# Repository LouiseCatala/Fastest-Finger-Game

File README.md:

# FASTEST FINGER — Made by Catala

This is an **editable KiCad PCB Editor board layout** recreated from the supplied reference image.

**Changes from the reference**
- All six names across the top have been removed.
- The bottom-center text now reads **Made by Catala**.
- The original title, three-player layout, approximate placement, and white decorative graphics are retained.

## PCB 3D Preview

The 3D visualization of the Fastest Finger PCB design created using KiCad.

## Schematic Diagram

The preliminary schematic diagram of the Fastest Finger circuit designed using KiCad Schematic Editor.

## Open in KiCad

1. Extract the whole ZIP; keep the `models` folder with the project files.
2. In KiCad Project Manager choose **File → Open Project** and select `Fastest_Finger_Made_by_Catala.kicad_pro`.
3. Double-click `Fastest_Finger_Made_by_Catala.kicad_pcb` from the project tree, or choose the PCB Editor shortcut.
4. In PCB Editor, use **View → 3D Viewer** (`Alt+3` on many systems) to see the approximate component models.
5. Edit text and locations directly on the **F.SilkS** and other PCB layers.
6. Open **Schematic Editor** to view or modify the `.kicad_sch` file.

Alternatively, start standalone PCB Editor and use **File → Open** to select the `.kicad_pcb` file. Do not try to select `.kicad_pcb` from KiCad Project Manager's **Open Project** file dialog, which filters for `.kicad_pro`.

## Hardware Components

| Component | Quantity |
|-----------|----------|
| Tang Nano 9K FPGA Board | 1 |
| 4-Digit 7-Segment Display | 1 |
| Player Push Buttons | 3 |
| START Button | 1 |
| RESET Button | 1 |
| NPN Transistors | 5 |
| Resistors | 17 |
| Capacitors | 2 |
| Diodes | 4 |
| LEDs | 2 |
| Buzzer | 1 |
| Mounting Holes | 4 |
| Printed Circuit Board | 1 |

## Important Limitation

This is a **visual/layout reconstruction with a preliminary schematic, not a verified, manufacturing-ready electronic design**.

The electrical connections, FPGA pin assignments, component values, and control wiring require verification. PCB traces are not fully routed, and FPGA code is not included.

Do not send the PCB for fabrication or assume functionality without verifying the actual circuit.

Real footprints and dimensions must be checked against the specific parts to be installed, especially the four-digit display, buttons, buzzer, and diodes. Visual models are approximations, not manufacturer STEP models.

- Board nominal dimensions: **174 mm × 128 mm**.
- Tang Nano 9K: represented by a **2 × 24 pin, 2.54 mm pitch** carrier footprint.
- Editable silkscreen labels and PCB features are part of the `.kicad_pcb` file.

---

**Made by Catala**

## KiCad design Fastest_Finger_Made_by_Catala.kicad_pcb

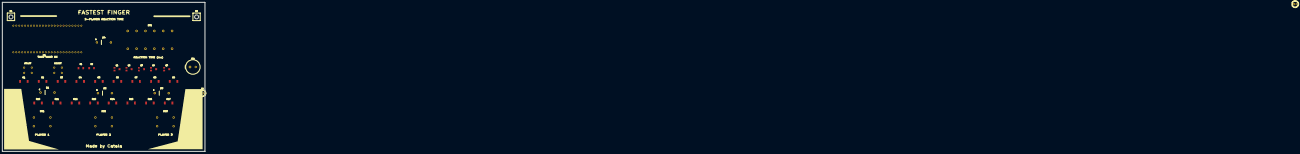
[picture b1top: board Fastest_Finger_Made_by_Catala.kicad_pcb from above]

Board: 2 copper layers, 174.0 x 128.0 mm, 42 parts (0 on the bottom side), 38 nets, no tracks yet.

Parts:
BZ1: Buzzer_TDK_PS1240P02BT_D12.2mm_H6.5mm
C1, C2: Capacitor; Cap_1206
D1, D2, D3, D4: Diode; Diode_DO41_P7.62
D5, D6: LED_D5.0mm
DS1: 4-digit display; Display_4Digit_7Segment_54x21
H1, H2, H3, H4: Mounting Hole; MountingHole_3.4mm
Q1, Q2, Q3, Q4, Q5: Transistor; SOT23_3Pin
R1, R2, R3, R4, R5, R6, R7, R8, R9, R10, R11, R12, R13, R14, R15, R16, R17: R; Resistor_2512
SW1, SW2, SW3: Pushbutton 12 mm; SW_Tact_12mm
SW4, SW5: Pushbutton 6 mm; SW_Tact_6mm
U1: Tang Nano 9K; Tang_Nano_9K_2x24

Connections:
+3V3: BZ1.1, C1.1, C2.1, R13.1, R14.1, R15.1, R16.1, U1.1
BTN_P1: R13.2, SW1.1, U1.3
BTN_P2: R14.2, SW2.1, U1.4
BTN_P3: R15.2, SW3.1, U1.5
BTN_RESET: SW5.1, U1.7
BTN_START: R16.2, SW4.1, U1.6
BUZZ_BASE: Q5.1, R17.2
BUZZ_GPIO: R17.1, U1.20
BUZZ_NEG: BZ1.2, Q5.3
DIG1: DS1.12, Q1.3
DIG1_BASE: Q1.1, R9.2
DIG1_GPIO: R9.1, U1.16
DIG2: DS1.9, Q2.3
DIG2_BASE: Q2.1, R10.2
DIG2_GPIO: R10.1, U1.17
DIG3: DS1.8, Q3.3
DIG3_BASE: Q3.1, R11.2
DIG3_GPIO: R11.1, U1.18
DIG4: DS1.6, Q4.3
DIG4_BASE: Q4.1, R12.2
DIG4_GPIO: R12.1, U1.19
GND: C1.2, C2.2, Q1.2, Q2.2, Q3.2, Q4.2, Q5.2, SW1.2, SW2.2, SW3.2, SW4.2, SW5.2, U1.2
SEG_A: DS1.11, R1.2
SEG_A_GPIO: R1.1, U1.8
SEG_B: DS1.7, R2.2
SEG_B_GPIO: R2.1, U1.9
SEG_C: DS1.4, R3.2
SEG_C_GPIO: R3.1, U1.10
SEG_D: DS1.2, R4.2
SEG_DP: DS1.3, R8.2
SEG_DP_GPIO: R8.1, U1.15
SEG_D_GPIO: R4.1, U1.11
SEG_E: DS1.1, R5.2
SEG_E_GPIO: R5.1, U1.12
SEG_F: DS1.10, R6.2
SEG_F_GPIO: R6.1, U1.13
SEG_G: DS1.5, R7.2
SEG_G_GPIO: R7.1, U1.14
